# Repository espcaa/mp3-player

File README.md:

[{BOM}](https://github.com/espcaa/mp3-player/blob/main/BOM.md) - [{JOURNAL}](https://github.com/espcaa/mp3-player/blob/main/JOURNAL.md) - [{PCB}](https://kicanvas.org/?repo=https%3A%2F%2Fgithub.com%2Fespcaa%2Fmp3-player%2Ftree%2Fmain%2Fsrc%2Fkicad) - [{FIRMWARE}](https://github.com/espcaa/mp3-player/blob/main/src/firmware) - [{CAD}](https://cad.onshape.com/documents/df238a6328d0735d97863cef/w/6197d36ae28a3603accb47f3/e/8dee80f336b142ce4e5ee150?renderMode=0&uiState=6a380bcfd7346ceef4261340)

# mp3-player

A minimalist open source pocket sized¹ mp3 player\
\
(¹ if your pocket is big enough to fit a 115mmx50mmx20mm brick)

## Why did I even build this?

I bring my phone every time, everywhere I go. My main excuse is that I need it for music, but that's not usually what ends up happening... So I built this to have a dedicated music player that I could bring with me when I don't need a phone! (mainly high school or going for a walk)\
I also wanted to learn how to design a more complex & integrated pcb!\
\
If you find this cool, you should read [the journal](https://github.com/espcaa/mp3-player/blob/main/JOURNAL.md) I kept while designing this!

## Overview

**Specs**:

- mcu: rp2350b
- bluetooth module: fsc-BT1114QI
- dac: PCM5102A
- power: 505050 battery + BQ24075 power path ic
- pcb: 4 layer (signal, ground, power, signal) 115mmx50mm
- case: 3d printed

**Features**:

- full size sdcard slot
- 2.8 inch high definition color display (480x640, around 286 dpi)
- custom themes
- 3.5mm headphone jack
- bluetooth le + classic support
- modern and clean ui

## Hardware

_pcb & cad screenshots_
\
\
The brain is a 4 layer hand routed pcb, designed to be compact & cheap to manufacture (jlcpcb 4 layers basic tolerances).\
I first planned to use a nrf chip for the audio but finally moved to a feasycom module to support classic A2DP bluetooth audio (basically everything that is not recent/high end) because I realized my headphones were not le compatible (but now my new ones are!).\
Full size sdcard support is because I wanted to be able to use my mac's sdcard reader to easily transfer new music + not lose super small micro sd cards.\
I also originally wanted to make the case in transparent resin, but I ended up choosing 3d printing for multiple reasons:

- way cheaper
- faster to iterate on
- petg is way more shock resistant than resin
- faster to get a finished project

[explore the board & schematics in your browser](https://kicanvas.org/?repo=https%3A%2F%2Fgithub.com%2Fespcaa%2Fmp3-player%2Ftree%2Fmain%2Fsrc%2Fkicad)

## Firmware

_warning: this is a wip and some parts of the firmware have been ai generated to get a poc working quickly, but I plan to rewrite it very soon._ \
\
The firmware is written in c and uses the pico sdk. I also wrote a desktop simulator that allows you to test ui changes without reflashing all the time/having the device.

**Building to run on device:**

_If you just need an already built uf2, you can just grab it from the releases page or directly from the actions tab (action runs on every commit inside src/firmware)_
\
\
(You need cmake, a pico sdk, an arm-none-eabi toolchain, pico-extras installed)

- clone this repo
- export these env vars:
  - `PICO_SDK_PATH` -> path to pico-sdk
  - `PICO_TOOLCHAIN_PATH` -> path to an arm-none-eabi toolchain (`Applications/ArmGNUToolchain/15.2.rel1/arm-none-eabi/bin` on my laptop)
  - `PICO_EXTRAS_PATH` -> path to pico-extras
- go to src/firmware/ & run `./build_pico.sh --clean`
- flash the uf2 via usb (hold BOOTSEL while plugging in the device, then drag the uf2 to the mounted drive)

**Building to run on desktop:**

_(this allows you to run/test the same ui on your computer without flashing the device!)_\
_(you need sdl2 installed)_

- go to src/firmware/ & run `./run_emulator.sh --clean`

## License

Firmware is MIT, hardware is CERN-OHL-S, and the 3d files + docs are CC-BY-SA.\
See [LICENSE](LICENSE) for details.\
\
\

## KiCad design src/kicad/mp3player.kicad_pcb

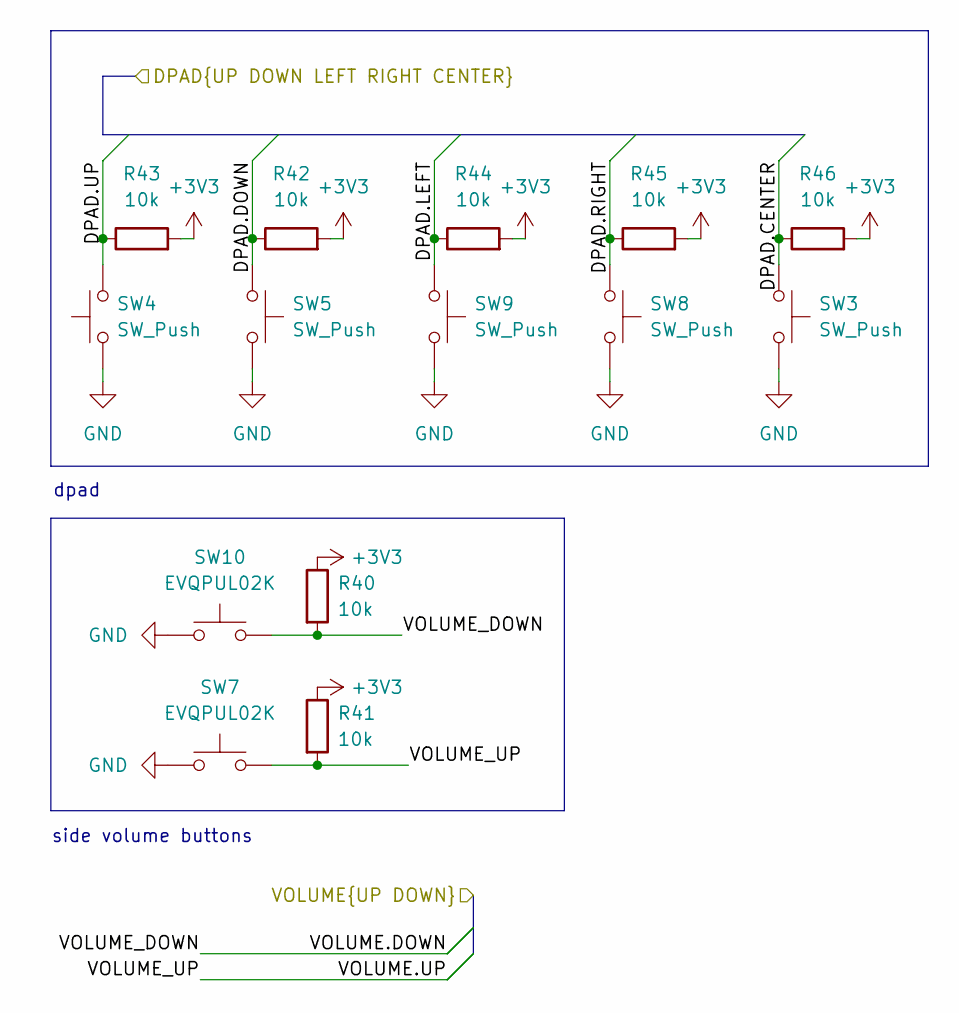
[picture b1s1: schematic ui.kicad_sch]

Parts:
R40, R41, R42, R43, R44, R45, R46: 10k; R_0402_1005Metric; LCSC Part C2906861
SW3, SW4, SW5, SW8, SW9: SW_Push; SW-SMD_4P-L6.2-W6.2-P4.00-LS6.8; LCSC Part C115354
SW7, SW10: EVQPUL02K; KEY-SMD_4P-L4.7-W3.5-P1.70-LS6.4-EH; LCSC Part C79175

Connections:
+3V3: R40.1, R41.1, R42.2, R43.2, R44.2, R45.2, R46.2; also elsewhere on the board
/processing/DPAD.CENTER: R46.1, SW3.1; also elsewhere on the board
/processing/DPAD.DOWN: R42.1, SW5.1; also elsewhere on the board
/processing/DPAD.LEFT: R44.1, SW9.1; also elsewhere on the board
/processing/DPAD.RIGHT: R45.1, SW8.1; also elsewhere on the board
/processing/DPAD.UP: R43.1, SW4.2; also elsewhere on the board
/processing/VOLUME.DOWN: R40.2, SW10.1; also elsewhere on the board
/processing/VOLUME.UP: R41.2, SW7.2; also elsewhere on the board
GND: SW3.2, SW4.1, SW5.2, SW7.1, SW8.2, SW9.2, SW10.2; also elsewhere on the board

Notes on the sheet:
dpad
side volume buttons

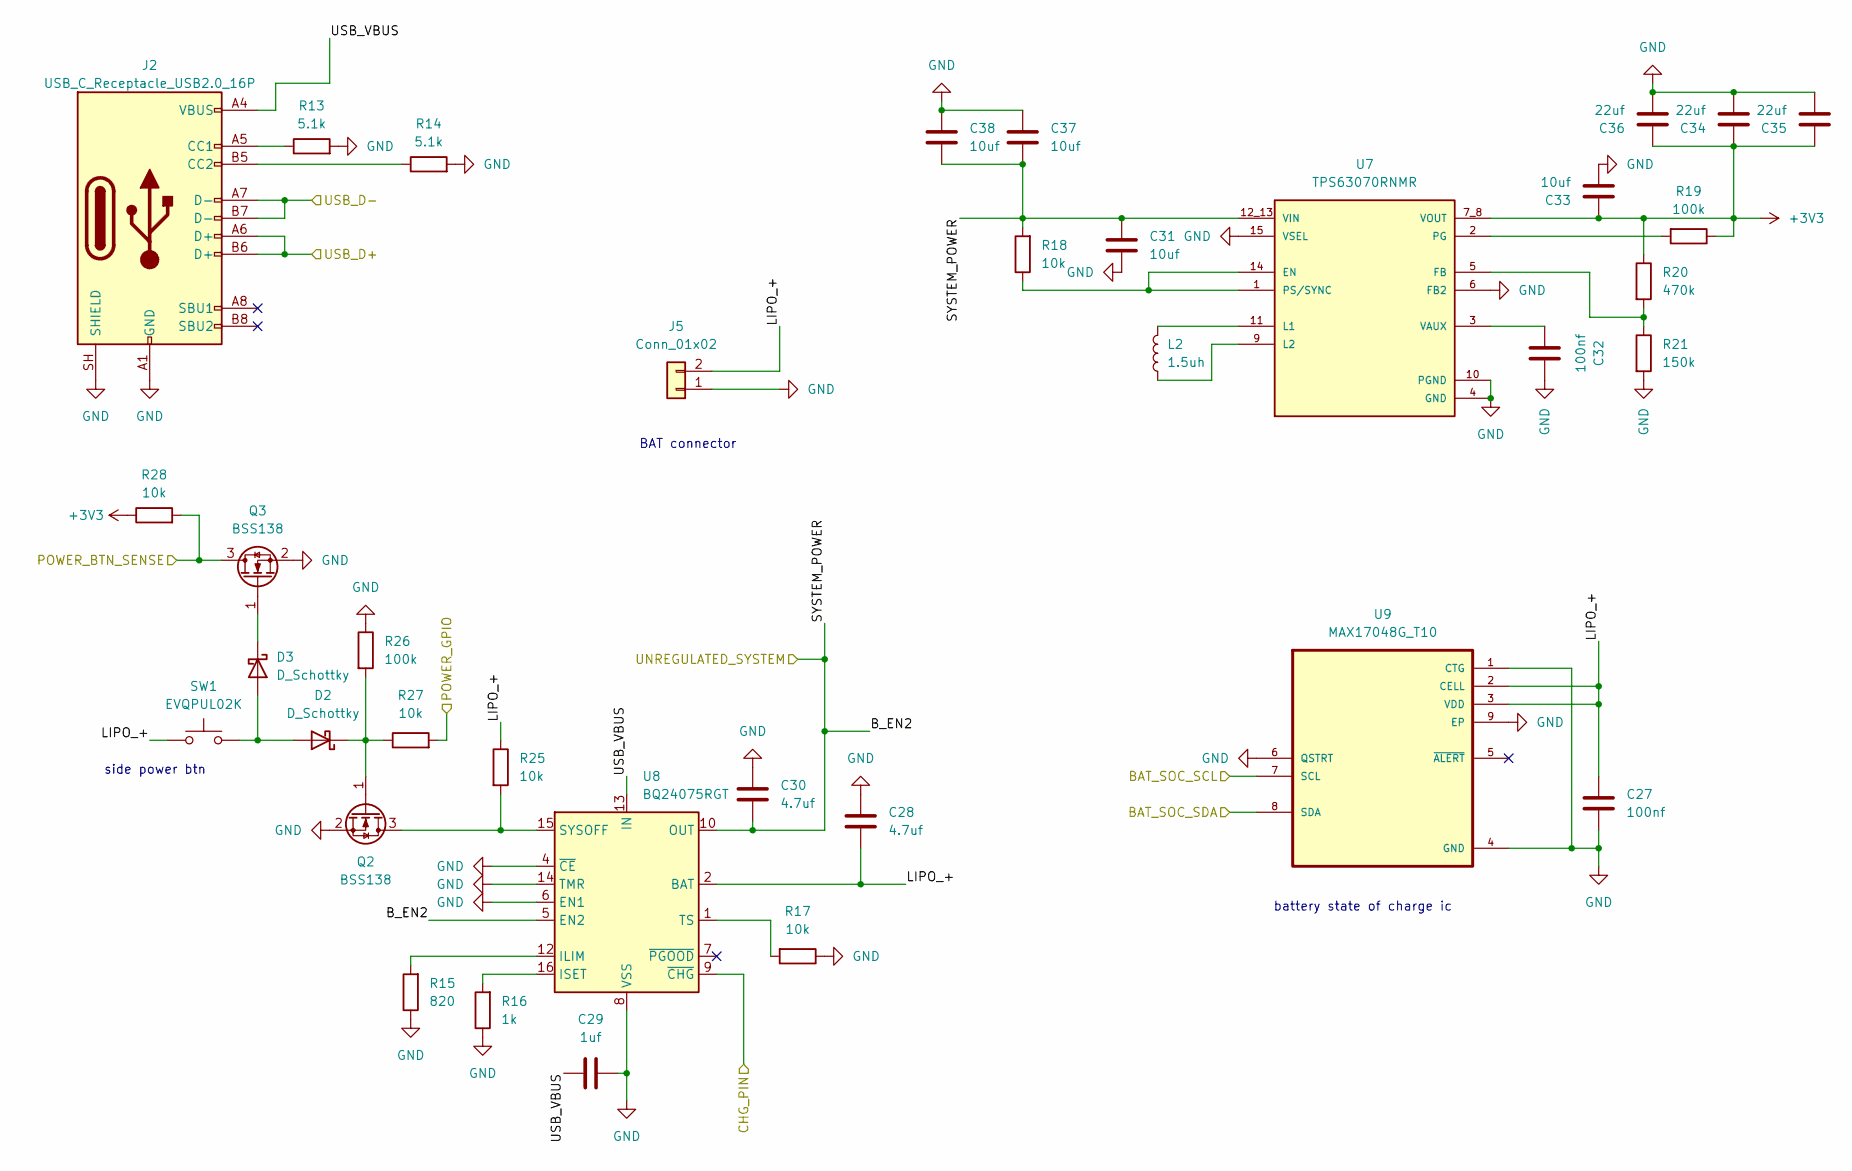
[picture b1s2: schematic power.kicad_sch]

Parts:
C27, C32: 100nf; C_0402_1005Metric; LCSC Part C1525
C28, C30: 4.7uf; C_0603_1608Metric; LCSC Part C19666
C29: 1uf; C_0402_1005Metric; LCSC Part C307427
C31, C33, C37, C38: 10uf; C_0603_1608Metric; LCSC Part C96446
C34, C35, C36: 22uf; C_0603_1608Metric; LCSC Part C59461
D2, D3: D_Schottky; D_SOD-123; LCSC Part C8598
J2: USB_C_Receptacle_USB2.0_16P; USB-C-SMD_GT-USB-7047C; LCSC Part C963218
J5: Conn_01x02; JST_PH_S2B-PH-SM4-TB_1x02-1MP_P2.00mm_Horizontal; LCSC Part C295747
L2: 1.5uh; L_Sunlord_MWSA0402S; LCSC Part C351088
Q2, Q3: BSS138; SOT-23; LCSC Part C52895
R13, R14: 5.1k; R_0402_1005Metric; LCSC Part C852856
R15: 820; R_0603_1608Metric; Tolerance 1%; LCSC Part C23253
R16: 1k; R_0402_1005Metric; Tolerance 1%; LCSC Part C852624
R17, R18, R25, R27, R28: 10k; R_0402_1005Metric; LCSC Part C2906861
R19, R26: 100k; R_0402_1005Metric; LCSC Part C481918
R20: 470k; R_0603_1608Metric; LCSC Part C2907040
R21: 150k; R_0603_1608Metric; LCSC Part C326734
SW1: EVQPUL02K; KEY-SMD_4P-L4.7-W3.5-P1.70-LS6.4-EH; LCSC Part C79175
U7: TPS63070RNMR; VREG_TPS63070RNMR; PARTREV B; LCSC Part C109322
U8: BQ24075RGT; VQFN-16-1EP_3x3mm_P0.5mm_EP1.6x1.6mm; LCSC Part C15464
U9: MAX17048G_T10; SON50P200X200X80-9N; LCSC Part C2682616

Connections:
+3V3: C33.1, C34.1, C35.1, C36.1, R19.1, R20.1, R28.1, U7.7_8 (VOUT); also elsewhere on the board
/power/B_EN2: C30.2, C31.1, C37.1, C38.2, R18.2, U7.12_13 (VIN), U8.5 (EN2), U8.10 (OUT), U8.11 (OUT); also elsewhere on the board
/power/CHG_PIN: U8.9 (~CHG); also elsewhere on the board
/power/LIPO_+: C27.1, C28.2, J5.2, R25.1, SW1.1, U8.2 (BAT), U8.3 (BAT), U9.2 (CELL), U9.3 (VDD)
/power/POWER_BTN_SENSE: Q3.3 (D), R28.2; also elsewhere on the board
/power/POWER_GPIO: R27.2; also elsewhere on the board
/power/USB_D+: J2.A6 (D+), J2.B6 (D+); also elsewhere on the board
/power/USB_D-: J2.A7 (D-), J2.B7 (D-); also elsewhere on the board
/power/USB_VBUS: C29.2, J2.A4 (VBUS), J2.A9 (VBUS), J2.B4 (VBUS), J2.B9 (VBUS), U8.13 (IN)
/processing/I2C_SCL: U9.7 (SCL); also elsewhere on the board
/processing/I2C_SDA: U9.8 (SDA); also elsewhere on the board
GND: C27.2, C28.1, C29.1, C30.1, C31.2, C32.2, C33.2, C34.2, C35.2, C36.2, C37.2, C38.1, J2.A1 (GND), J2.A12 (GND), J2.B1 (GND), J2.B12 (GND), J2.SH (SHIELD), J5.1, Q2.2 (S), Q3.2 (S), R13.2, R14.2, R15.1, R16.1, R17.1, R21.2, R26.1, U7.4 (GND), U7.6 (FB2), U7.10 (PGND), U7.15 (VSEL), U8.4 (~CE), U8.6 (EN1), U8.8 (VSS), U8.14 (TMR), U8.17 (VSS), U9.1 (CTG), U9.4 (GND), U9.6 (QSTRT), U9.9 (EP); also elsewhere on the board
unnamed: D2.2 (A), D3.2 (A), SW1.2
unnamed: D2.1 (K), Q2.1 (G), R26.2, R27.1
unnamed: D3.1 (K), Q3.1 (G)
unnamed: J2.A5 (CC1), R13.1
unnamed: J2.B5 (CC2), R14.1
unnamed: Q2.3 (D), R25.2, U8.15 (SYSOFF)
unnamed: R18.1, U7.1 (PS/SYNC), U7.14 (EN)
unnamed: R20.2, R21.1, U7.5 (FB)
unnamed: L2.2, U7.11 (L1)
unnamed: L2.1, U7.9 (L2)
unnamed: R19.2, U7.2 (PG)
unnamed: C32.1, U7.3 (VAUX)
unnamed: R15.2, U8.12 (ILIM)
unnamed: R16.2, U8.16 (ISET)
unnamed: R17.2, U8.1 (TS)

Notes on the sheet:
battery state of charge ic
BAT connector
side power btn

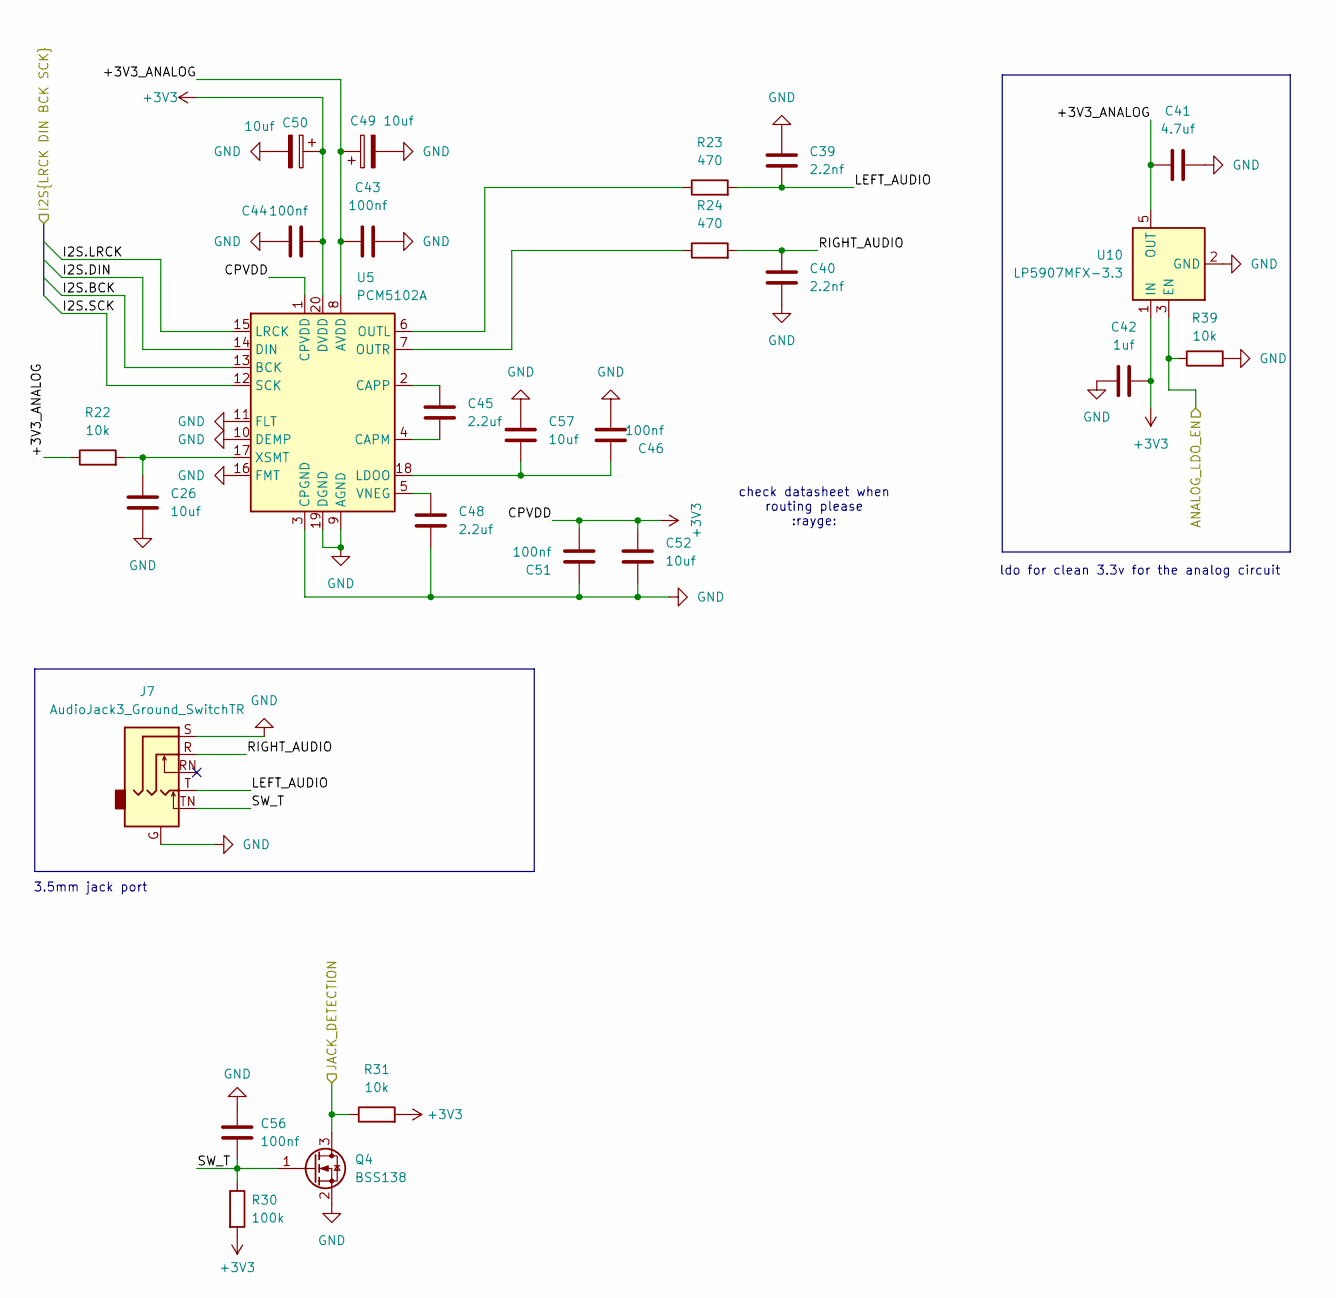
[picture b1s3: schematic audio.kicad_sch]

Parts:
C26, C49, C50: 10uf; C_0603_1608Metric; LCSC Part C96446
C39, C40: 2.2nf; C_0805_2012Metric; LCSC Part C28260
C41: 4.7uf; C_0603_1608Metric; LCSC Part C19666
C42: 1uf; C_0402_1005Metric; LCSC Part C307427
C43, C44, C46, C51, C56: 100nf; C_0402_1005Metric; LCSC Part C1525
C45, C48: 2.2uf; C_0402_1005Metric; LCSC Part C12530
C52, C57: 10uf; C_0805_2012Metric; LCSC Part C1713
J7: AudioJack3_Ground_SwitchTR; AUDIO-SMD_PJ-342-141; LCSC Part C7507452
Q4: BSS138; SOT-23; LCSC Part C52895
R22, R31, R39: 10k; R_0402_1005Metric; LCSC Part C2906861
R23, R24: 470; R_0603_1608Metric; Tolerance 1%; LCSC Part C218042
R30: 100k; R_0402_1005Metric; LCSC Part C481918
U5: PCM5102A; TSSOP-20_4.4x6.5mm_P0.65mm; LCSC Part C107671
U10: LP5907MFX-3.3; SOT-23-5; LCSC Part C23380874

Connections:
+3V3: C42.1, C44.1, C50.1, C51.1, C52.2, R30.2, R31.2, U5.1 (CPVDD), U5.20 (DVDD), U10.1 (IN); also elsewhere on the board
/audio/+3V3_ANALOG: C41.1, C43.1, C49.1, R22.1, U5.8 (AVDD), U10.5 (OUT)
/audio/ANALOG_LDO_EN: R39.1, U10.3 (EN); also elsewhere on the board
/audio/I2S.BCK: U5.13 (BCK); also elsewhere on the board
/audio/I2S.DIN: U5.14 (DIN); also elsewhere on the board
/audio/I2S.LRCK: U5.15 (LRCK); also elsewhere on the board
/audio/I2S.SCK: U5.12 (SCK); also elsewhere on the board
/audio/JACK_DETECTION: Q4.3 (D), R31.1; also elsewhere on the board
/audio/LEFT_AUDIO: C39.2, J7.T, R23.2
/audio/RIGHT_AUDIO: C40.1, J7.R, R24.2
/audio/SW_T: C56.2, J7.TN, Q4.1 (G), R30.1
GND: C26.2, C39.1, C40.2, C41.2, C42.2, C43.2, C44.2, C46.1, C48.1, C49.2, C50.2, C51.2, C52.1, C56.1, C57.2, J7.G, J7.S, Q4.2 (S), R39.2, U5.3 (CPGND), U5.9 (AGND), U5.10 (DEMP), U5.11 (FLT), U5.16 (FMT), U5.19 (DGND), U10.2 (GND); also elsewhere on the board
unnamed: C45.1, U5.4 (CAPM)
unnamed: C45.2, U5.2 (CAPP)
unnamed: C46.2, C57.1, U5.18 (LDOO)
unnamed: R23.1, U5.6 (OUTL)
unnamed: R24.1, U5.7 (OUTR)
unnamed: C48.2, U5.5 (VNEG)
unnamed: C26.1, R22.2, U5.17 (XSMT)

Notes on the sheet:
ldo for clean 3.3v for the analog circuit
3.5mm jack port
check datasheet when routing please :rayge:

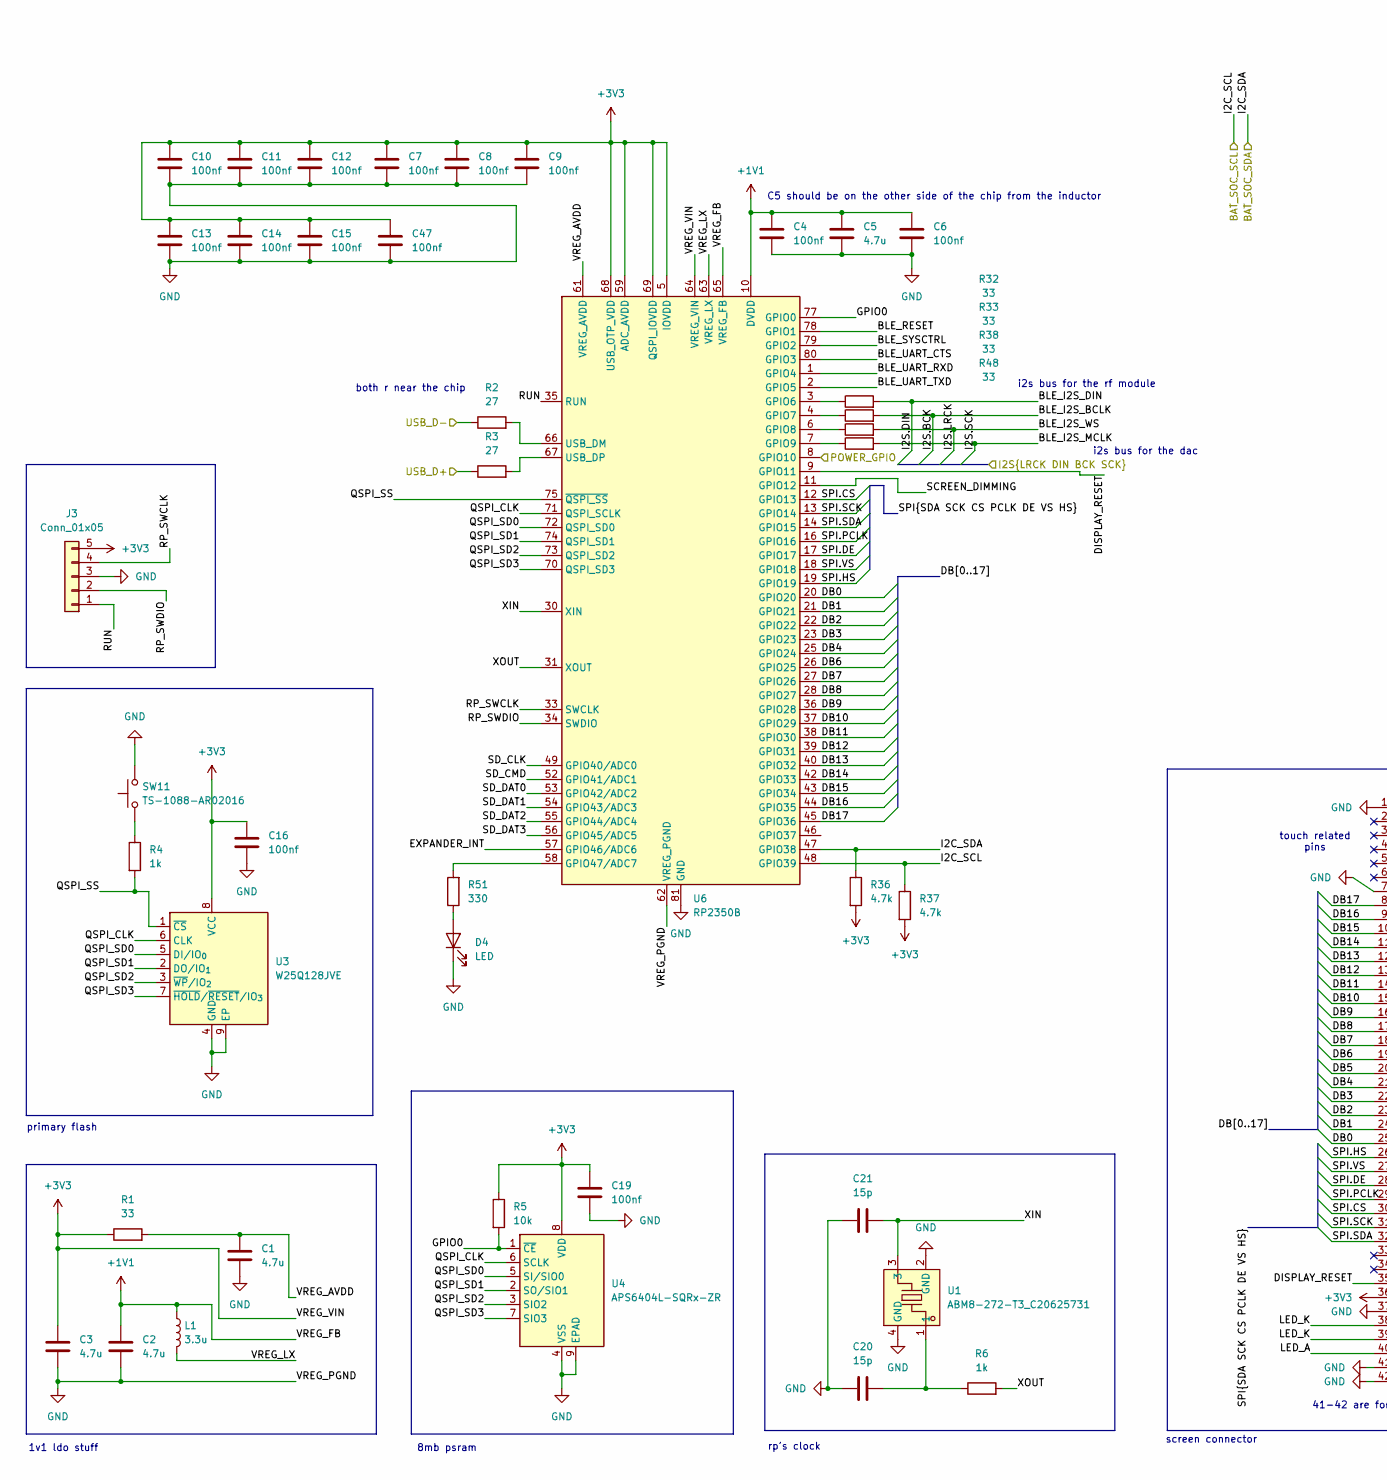
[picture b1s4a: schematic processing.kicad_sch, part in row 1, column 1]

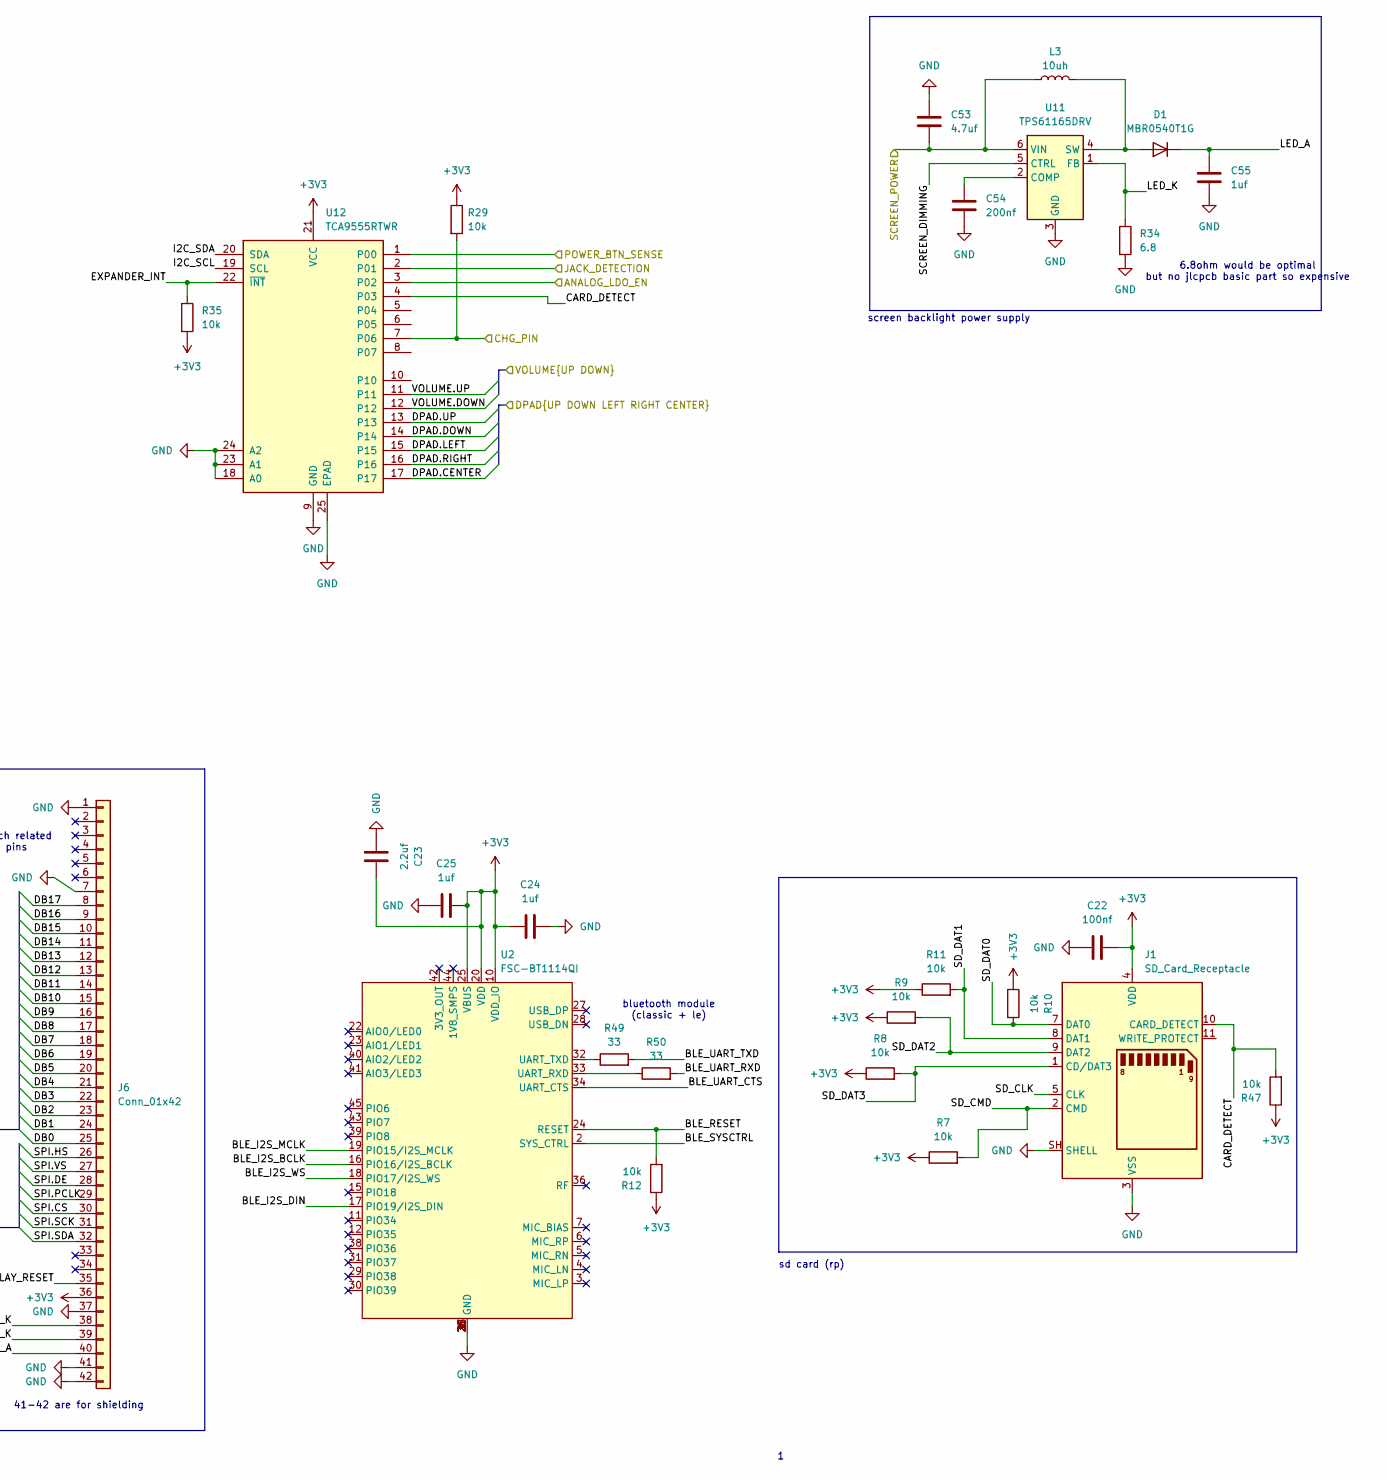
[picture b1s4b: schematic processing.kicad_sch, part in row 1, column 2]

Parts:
C1, C3, C5: 4.7u; C_0402_1005Metric; LCSC Part C23733
C2: 4.7u; C_0402_1005Metric; LCSC Part C368809
C4, C6, C7, C8, C9, C10, C11, C12, C13, C14, C15, C16, C19, C22, C47: 100nf; C_0402_1005Metric; LCSC Part C1525
C20, C21: 15p; C_0402_1005Metric; LCSC Part C1548
C23: 2.2uf; C_0402_1005Metric; LCSC Part C12530
C24, C25, C55: 1uf; C_0402_1005Metric; LCSC Part C307427
C53: 4.7uf; C_0603_1608Metric; LCSC Part C19666
C54: 200nf; C_0402_1005Metric; LCSC Part C16772
D1: MBR0540T1G; D_SOD-123; LCSC Part C21353
D4: LED; LED_0603_1608Metric; LCSC Part C2286
J1: SD_Card_Receptacle; SD-SMD_SD-006M; LCSC Part C125615
J3: Conn_01x05; test_pads; LCSC Part //
J6: Conn_01x42; FPC-SMD_AFC07-S40FCC00; LCSC Part C11062
L1: 3.3u; IND-SMD_L2.0-W1.6_AOTA-B201610S3R3-101-T; LCSC Part C42411119
L3: 10uh; L_TechFuse_SL0420; LCSC Part C22463809
R1, R32, R33, R38, R48, R49, R50: 33; R_0402_1005Metric; LCSC Part C2906931
R2, R3: 27; R_0402_1005Metric; LCSC Part C25105
R4, R6: 1k; R_0402_1005Metric; LCSC Part C852624
R5, R7, R8, R9, R10, R11, R12, R29, R35, R47: 10k; R_0402_1005Metric; LCSC Part C2906861
R34: 6.8; R_0603_1608Metric; Tolerance 1%; LCSC Part C2907056
R36, R37: 4.7k; R_0402_1005Metric; LCSC Part C2906941
R51: 330; R_0402_1005Metric; LCSC Part C71626
SW11: TS-1088-AR02016; SW-SMD_L3.9-W3.0-P4.45; LCSC Part C720477
U1: ABM8-272-T3_C20625731; CRYSTAL-SMD_4P-L3.2-W2.5-BL; MPN ABM8-272-T3; LCSC Part C20625731
U2: FSC-BT1114QI; LCSC Part //
U3: W25Q128JVE; WSON-8-1EP_8x6mm_P1.27mm_EP3.4x4.3mm; LCSC Part C2456297
U4: APS6404L-SQRx-ZR; Winbond_USON-8-1EP_3x2mm_P0.5mm_EP0.2x1.6mm; LCSC Part C3040877
U6: RP2350B; QFN-80-1EP_10x10mm_P0.4mm_EP3.4x3.4mm; LCSC Part C42415655
U11: TPS61165DRV; WSON-6-1EP_2x2mm_P0.65mm_EP1x1.6mm; LCSC Part C122568
U12: TCA9555RTWR; WQFN-24-1EP_4x4mm_P0.5mm_EP2.45x2.45mm; LCSC Part C140277

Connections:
+1V1: C2.1, C4.1, C5.1, C6.1, L1.1, U6.10 (DVDD), U6.32 (DVDD), U6.51 (DVDD), U6.65 (VREG_FB)
+3V3: C3.1, C7.1, C8.1, C9.1, C10.1, C11.1, C12.1, C13.1, C14.1, C15.1, C16.1, C19.2, C22.2, C23.2, C24.1, C25.1, C47.1, J1.4 (VDD), J3.5, J6.36, R1.1, R5.1, R7.1, R8.1, R9.1, R10.1, R11.1, R12.1, R29.1, R35.2, R36.2, R37.2, R47.1, U2.10 (VDD_IO), U2.20 (VDD), U2.25 (VBUS), U3.8 (VCC), U4.8 (VDD), U6.5 (IOVDD), U6.15 (IOVDD), U6.24 (IOVDD), U6.29 (IOVDD), U6.41 (IOVDD), U6.50 (IOVDD), U6.59 (ADC_AVDD), U6.60 (IOVDD), U6.64 (VREG_VIN), U6.68 (USB_OTP_VDD), U6.69 (QSPI_IOVDD), U6.76 (IOVDD), U12.21 (VCC); also elsewhere on the board
/audio/ANALOG_LDO_EN: U12.3 (P02); also elsewhere on the board
/audio/I2S.BCK: R33.2, U2.16 (PIO16/I2S_BCLK); also elsewhere on the board
/audio/I2S.DIN: R32.2, U2.17 (PIO19/I2S_DIN); also elsewhere on the board
/audio/I2S.LRCK: R38.2, U2.18 (PIO17/I2S_WS); also elsewhere on the board
/audio/I2S.SCK: R48.2, U2.19 (PIO15/I2S_MCLK); also elsewhere on the board
/audio/JACK_DETECTION: U12.2 (P01); also elsewhere on the board
/power/B_EN2: C53.2, L3.1, U11.6 (VIN); also elsewhere on the board
/power/CHG_PIN: R29.2, U12.7 (P06); also elsewhere on the board
/power/POWER_BTN_SENSE: U12.1 (P00); also elsewhere on the board
/power/POWER_GPIO: U6.8 (GPIO10); also elsewhere on the board
/power/USB_D+: R3.1; also elsewhere on the board
/power/USB_D-: R2.1; also elsewhere on the board
/processing/BLE_RESET: R12.2, U2.24 (RESET), U6.78 (GPIO1)
/processing/BLE_SYSCTRL: U2.2 (SYS_CTRL), U6.79 (GPIO2)
/processing/BLE_UART_CTS: U2.34 (UART_CTS), U6.80 (GPIO3)
/processing/BLE_UART_RXD: R50.2, U6.1 (GPIO4)
/processing/BLE_UART_TXD: R49.2, U6.2 (GPIO5)
/processing/CARD_DETECT: J1.10 (CARD_DETECT), R47.2, U12.4 (P03)
/processing/DB0: J6.25, U6.20 (GPIO20)
/processing/DB1: J6.24, U6.21 (GPIO21)
/processing/DB2: J6.23, U6.22 (GPIO22)
/processing/DB3: J6.22, U6.23 (GPIO23)
/processing/DB4: J6.21, U6.25 (GPIO24)
/processing/DB5: J6.20
/processing/DB6: J6.19, U6.26 (GPIO25)
/processing/DB7: J6.18, U6.27 (GPIO26)
/processing/DB8: J6.17, U6.28 (GPIO27)
/processing/DB9: J6.16, U6.36 (GPIO28)
/processing/DB10: J6.15, U6.37 (GPIO29)
/processing/DB11: J6.14, U6.38 (GPIO30)
/processing/DB12: J6.13, U6.39 (GPIO31)
/processing/DB13: J6.12, U6.40 (GPIO32)
/processing/DB14: J6.11, U6.42 (GPIO33)
/processing/DB15: J6.10, U6.43 (GPIO34)
/processing/DB16: J6.9, U6.44 (GPIO35)
/processing/DB17: J6.8, U6.45 (GPIO36)
/processing/DISPLAY_RESET: J6.35, U6.9 (GPIO11)
/processing/DPAD.CENTER: U12.17; also elsewhere on the board
/processing/DPAD.DOWN: U12.14; also elsewhere on the board
/processing/DPAD.LEFT: U12.15; also elsewhere on the board
/processing/DPAD.RIGHT: U12.16; also elsewhere on the board
/processing/DPAD.UP: U12.13; also elsewhere on the board
/processing/EXPANDER_INT: R35.1, U6.57 (GPIO46/ADC6), U12.22 (~INT)
/processing/GPIO0: R5.2, U4.1 (~CE), U6.77 (GPIO0)
/processing/I2C_SCL: R37.1, U6.48 (GPIO39), U12.19 (SCL); also elsewhere on the board
/processing/I2C_SDA: R36.1, U6.47 (GPIO38), U12.20 (SDA); also elsewhere on the board
/processing/LED_A: C55.2, D1.1 (K), J6.40
/processing/LED_K: J6.38, J6.39, R34.1, U11.1 (FB)
/processing/QSPI_CLK: U3.6 (CLK), U4.6 (SCLK), U6.71 (QSPI_SCLK)
/processing/QSPI_SD0: U3.5 (DI/IO_{0}), U4.5 (SI/SIO0), U6.72 (QSPI_SD0)
/processing/QSPI_SD1: U3.2 (DO/IO_{1}), U4.2 (SO/SIO1), U6.74 (QSPI_SD1)
/processing/QSPI_SD2: U3.3 (~WP/IO_{2}), U4.3 (SIO2), U6.73 (QSPI_SD2)
/processing/QSPI_SD3: U3.7 (~HOLD/~RESET/IO_{3}), U4.7 (SIO3), U6.70 (QSPI_SD3)
/processing/QSPI_SS: R4.2, U3.1 (~CS), U6.75 (~QSPI_SS)
/processing/RP_SWCLK: J3.4, U6.33 (SWCLK)
/processing/RP_SWDIO: J3.2, U6.34 (SWDIO)
/processing/RUN: J3.1, U6.35 (RUN)
/processing/SCREEN_DIMMING: U6.11 (GPIO12), U11.5 (CTRL)
/processing/SD_CLK: J1.5 (CLK), U6.49 (GPIO40/ADC0)
/processing/SD_CMD: J1.2 (CMD), R7.2, U6.52 (GPIO41/ADC1)
/processing/SD_DAT0: J1.7 (DAT0), R10.2, U6.53 (GPIO42/ADC2)
/processing/SD_DAT1: J1.8 (DAT1), R11.2, U6.54 (GPIO43/ADC3)
/processing/SD_DAT2: J1.9 (DAT2), R9.2, U6.55 (GPIO44/ADC4)
/processing/SD_DAT3: J1.1 (CD/DAT3), R8.2, U6.56 (GPIO45/ADC5)
/processing/SPI.CS: J6.30, U6.12 (GPIO13)
/processing/SPI.DE: J6.28, U6.17 (GPIO17)
/processing/SPI.HS: J6.26, U6.19 (GPIO19)
/processing/SPI.PCLK: J6.29, U6.16 (GPIO16)
/processing/SPI.SCK: J6.31, U6.13 (GPIO14)
/processing/SPI.SDA: J6.32, U6.14 (GPIO15)
/processing/SPI.VS: J6.27, U6.18 (GPIO18)
/processing/VOLUME.DOWN: U12.12; also elsewhere on the board
/processing/VOLUME.UP: U12.11; also elsewhere on the board
/processing/VREG_AVDD: C1.1, R1.2, U6.61 (VREG_AVDD)
/processing/VREG_LX: L1.2, U6.63 (VREG_LX)
/processing/XIN: C21.2, U1.3, U6.30 (XIN)
/processing/XOUT: R6.2, U6.31 (XOUT)
GND: C1.2, C2.2, C3.2, C4.2, C5.2, C6.2, C7.2, C8.2, C9.2, C10.2, C11.2, C12.2, C13.2, C14.2, C15.2, C16.2, C19.1, C20.1, C21.1, C22.1, C23.1, C24.2, C25.2, C47.2, C53.1, C54.2, C55.1, D4.1 (K), J1.3 (VSS), J1.6 (VSS), J1.SH (SHELL), J3.3, J6.1, J6.7, J6.37, J6.41, J6.42, R34.2, SW11.2, U1.2 (GND), U1.4 (GND), U2.1 (GND), U2.21 (GND), U2.26 (GND), U2.35 (GND), U2.37 (GND), U3.4 (GND), U3.9 (EP), U4.4 (VSS), U4.9 (EPAD), U6.62 (VREG_PGND), U6.81 (GND), U11.3 (GND), U11.7 (GND), U12.9 (GND), U12.18 (A0), U12.23 (A1), U12.24 (A2), U12.25 (EPAD); also elsewhere on the board
unnamed: C20.2, R6.1, U1.1
unnamed: D1.2 (A), L3.2, U11.4 (SW)
unnamed: D4.2 (A), R51.1
unnamed: R4.1, SW11.1
unnamed: R50.1, U2.33 (UART_RXD)
unnamed: R49.1, U2.32 (UART_TXD)
unnamed: R32.1, U6.3 (GPIO6)
unnamed: R33.1, U6.4 (GPIO7)
unnamed: R38.1, U6.6 (GPIO8)
unnamed: R48.1, U6.7 (GPIO9)
unnamed: R51.2, U6.58 (GPIO47/ADC7)
unnamed: R2.2, U6.66 (USB_DM)
unnamed: R3.2, U6.67 (USB_DP)
unnamed: C54.1, U11.2 (COMP)

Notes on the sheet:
bluetooth module (classic + le)
41-42 are for shielding
primary flash
rp's clock
8mb psram
C5 should be on the other side of the chip from the inductor
screen connector
both r near the chip
sd card (rp)
i2s bus for the rf module
6.8ohm would be optimal but no jlcpcb basic part so expensive
1v1 ldo stuff
i2s bus for the dac
screen backlight power supply
touch related pins

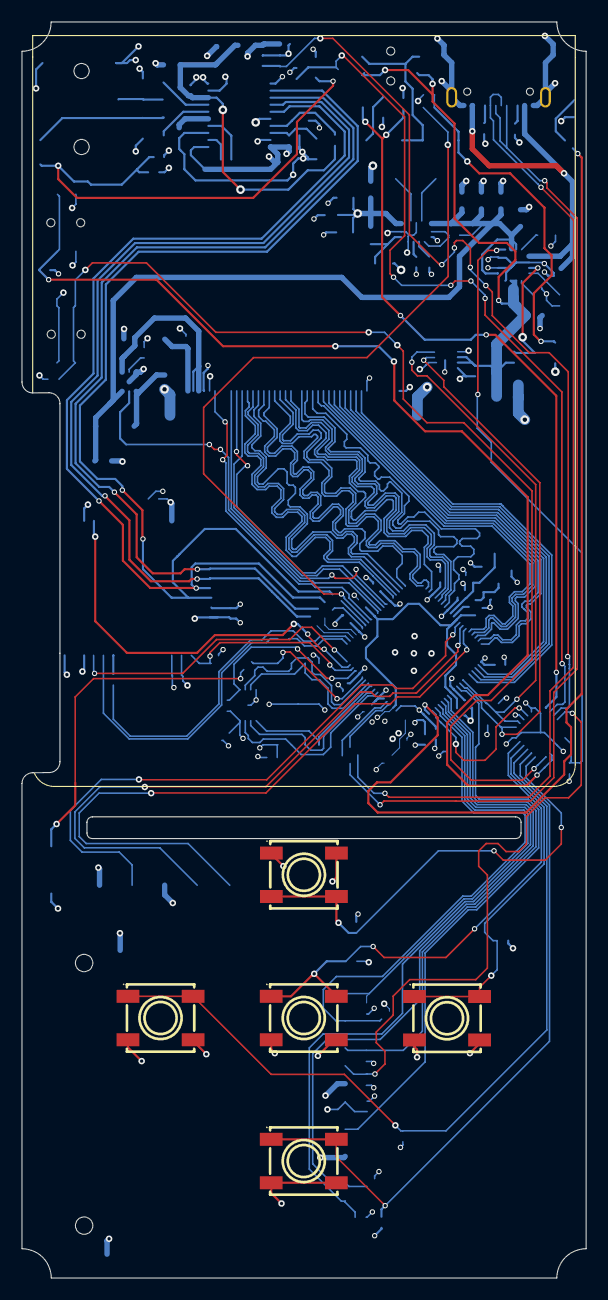
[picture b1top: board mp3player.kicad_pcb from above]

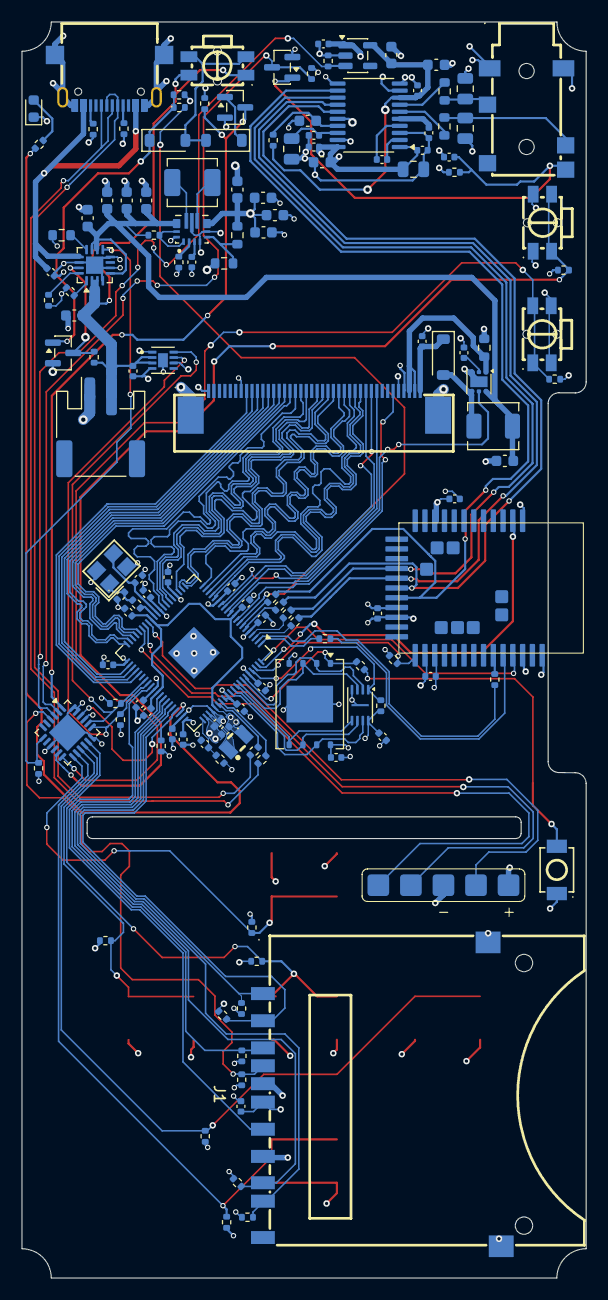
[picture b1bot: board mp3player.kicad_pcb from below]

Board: 4 copper layers, 52.0 x 115.7 mm, 143 parts (138 on the bottom side), 121 nets.

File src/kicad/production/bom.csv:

Designator,Footprint,Quantity,Value,LCSC Part #
"C1, C3, C5",0402,3,4.7u,C23733
"C10, C11, C12, C13, C14, C15, C16, C19, C22, C27, C32, C4, C43, C44, C46, C47, C51, C56, C6, C7, C8, C9",0402,22,100nf,C1525
C2,0402,1,4.7u,C368809
"C20, C21",0402,2,15p,C1548
"C23, C45, C48",0402,3,2.2uf,C12530
"C24, C25, C29, C42, C55",0402,5,1uf,C307427
"C26, C31, C33, C37, C38, C49, C50",0603,7,10uf,C96446
"C28, C30, C41, C53",0603,4,4.7uf,C19666
"C34, C35, C36",0603,3,22uf,C59461
"C39, C40",0805,2,2.2nf,C28260
"C52, C57",0805,2,10uf,C1713
C54,0402,1,200nf,C16772
D1,D_SOD-123,1,MBR0540T1G,C21353
"D2, D3",D_SOD-123,2,D_Schottky,C8598
D4,0603,1,LED,C2286
J1,SD-SMD_SD-006M,1,SD_Card_Receptacle,C125615
J2,USB-C-SMD_GT-USB-7047C,1,USB_C_Receptacle_USB2.0_16P,C963218
J5,JST_PH_S2B-PH-SM4-TB_1x02-1MP_P2.00mm_Horizontal,1,Conn_01x02,C295747
J6,FPC-SMD_AFC07-S40FCC00,1,Conn_01x42,C11062
J7,AUDIO-SMD_PJ-342-141,1,AudioJack3_Ground_SwitchTR,C7507452
L1,IND-SMD_L2.0-W1.6_AOTA-B201610S3R3-101-T,1,3.3u,C42411119
L2,L_Sunlord_MWSA0402S,1,1.5uh,C351088
L3,L_TechFuse_SL0420,1,10uh,C22463809
"Q2, Q3, Q4",SOT-23,3,BSS138,C52895
"R1, R32, R33, R38, R48, R49, R50",0402,7,33,C2906931
"R10, R11, R12, R17, R18, R22, R25, R27, R28, R29, R31, R35, R39, R40, R41, R42, R43, R44, R45, R46, R47, R5, R7, R8, R9",0402,25,10k,C2906861
"R13, R14",0402,2,5.1k,C852856
R15,0603,1,820,C23253
"R16, R4, R6",0402,3,1k,C852624
"R19, R26, R30",0402,3,100k,C481918
"R2, R3",0402,2,27,C25105
R20,0603,1,470k,C2907040
R21,0603,1,150k,C326734
"R23, R24",0603,2,470,C218042
R34,0603,1,6.8,C2907056
"R36, R37",0402,2,4.7k,C2906941
R51,0402,1,330,C71626
"SW1, SW10, SW7",KEY-SMD_4P-L4.7-W3.5-P1.70-LS6.4-EH,3,EVQPUL02K,C79175
SW11,SW-SMD_L3.9-W3.0-P4.45,1,TS-1088-AR02016,C720477
"SW3, SW4, SW5, SW8, SW9",SW-SMD_4P-L6.2-W6.2-P4.00-LS6.8,5,SW_Push,C115354
U1,CRYSTAL-SMD_4P-L3.2-W2.5-BL,1,ABM8-272-T3_C20625731,C20625731
U10,SOT-23-5,1,LP5907MFX-3.3,C23380874
U11,WSON-6-1EP_2x2mm_P0.65mm_EP1x1.6mm,1,TPS61165DRV,C122568
U12,WQFN-24-1EP_4x4mm_P0.5mm_EP2.45x2.45mm,1,TCA9555RTWR,C140277
U3,WSON-8-1EP_8x6mm_P1.27mm_EP3.4x4.3mm,1,W25Q128JVE,C2456297
U4,Winbond_USON-8-1EP_3x2mm_P0.5mm_EP0.2x1.6mm,1,APS6404L-SQRx-ZR,C3040877
U5,TSSOP-20_4.4x6.5mm_P0.65mm,1,PCM5102A,C107671
U6,QFN-80-1EP_10x10mm_P0.4mm_EP3.4x3.4mm,1,RP2350B,C42415655
U7,VREG_TPS63070RNMR,1,TPS63070RNMR,C109322
U8,VQFN-16-1EP_3x3mm_P0.5mm_EP1.6x1.6mm,1,BQ24075RGT,C15464
U9,SON50P200X200X80-9N,1,MAX17048G_T10,C2682616

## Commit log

2026-05-12 first commit!
2026-05-12 first pcb draft!
2026-05-12 markdown fix
2026-05-12 better recap :)
2026-05-12 oops
2026-05-12 again... (minor markdown fix)
2026-05-14 new journal entry & updated project files!!
2026-05-16 new day + schematic updates
2026-05-16 markdown fixes
2026-05-16 new journal entry!
2026-05-23 progress + new journal entry!
2026-05-28 may 28th
2026-05-29 more components associations
2026-05-29 may 29th + files updates
2026-05-31 routing + may 30th update + things
2026-05-31 markdown issues
2026-05-31 jun 1st what already noo
2026-06-01 first of june wo&
2026-06-03 new dayy
2026-06-04 new day!
2026-06-04 oops image
2026-06-04 final markdown fix
2026-06-12 12th
2026-06-12 image name fix
2026-06-12 ajdihuhsq
2026-06-14 pcb updates + journaling
2026-06-15 journal & files update
2026-06-17 june 18th update
2026-06-18 code update & journal
2026-06-19 battery indicator & icon system
2026-06-20 firmware/journal update
2026-06-20 journal update
2026-06-20 readme & journal
2026-06-20 readme fixes
2026-06-20 final readme fix :pray:
2026-06-21 makrdown fixes
2026-06-21 cad added + journal/bom update
2026-06-21 gh action + readme update
